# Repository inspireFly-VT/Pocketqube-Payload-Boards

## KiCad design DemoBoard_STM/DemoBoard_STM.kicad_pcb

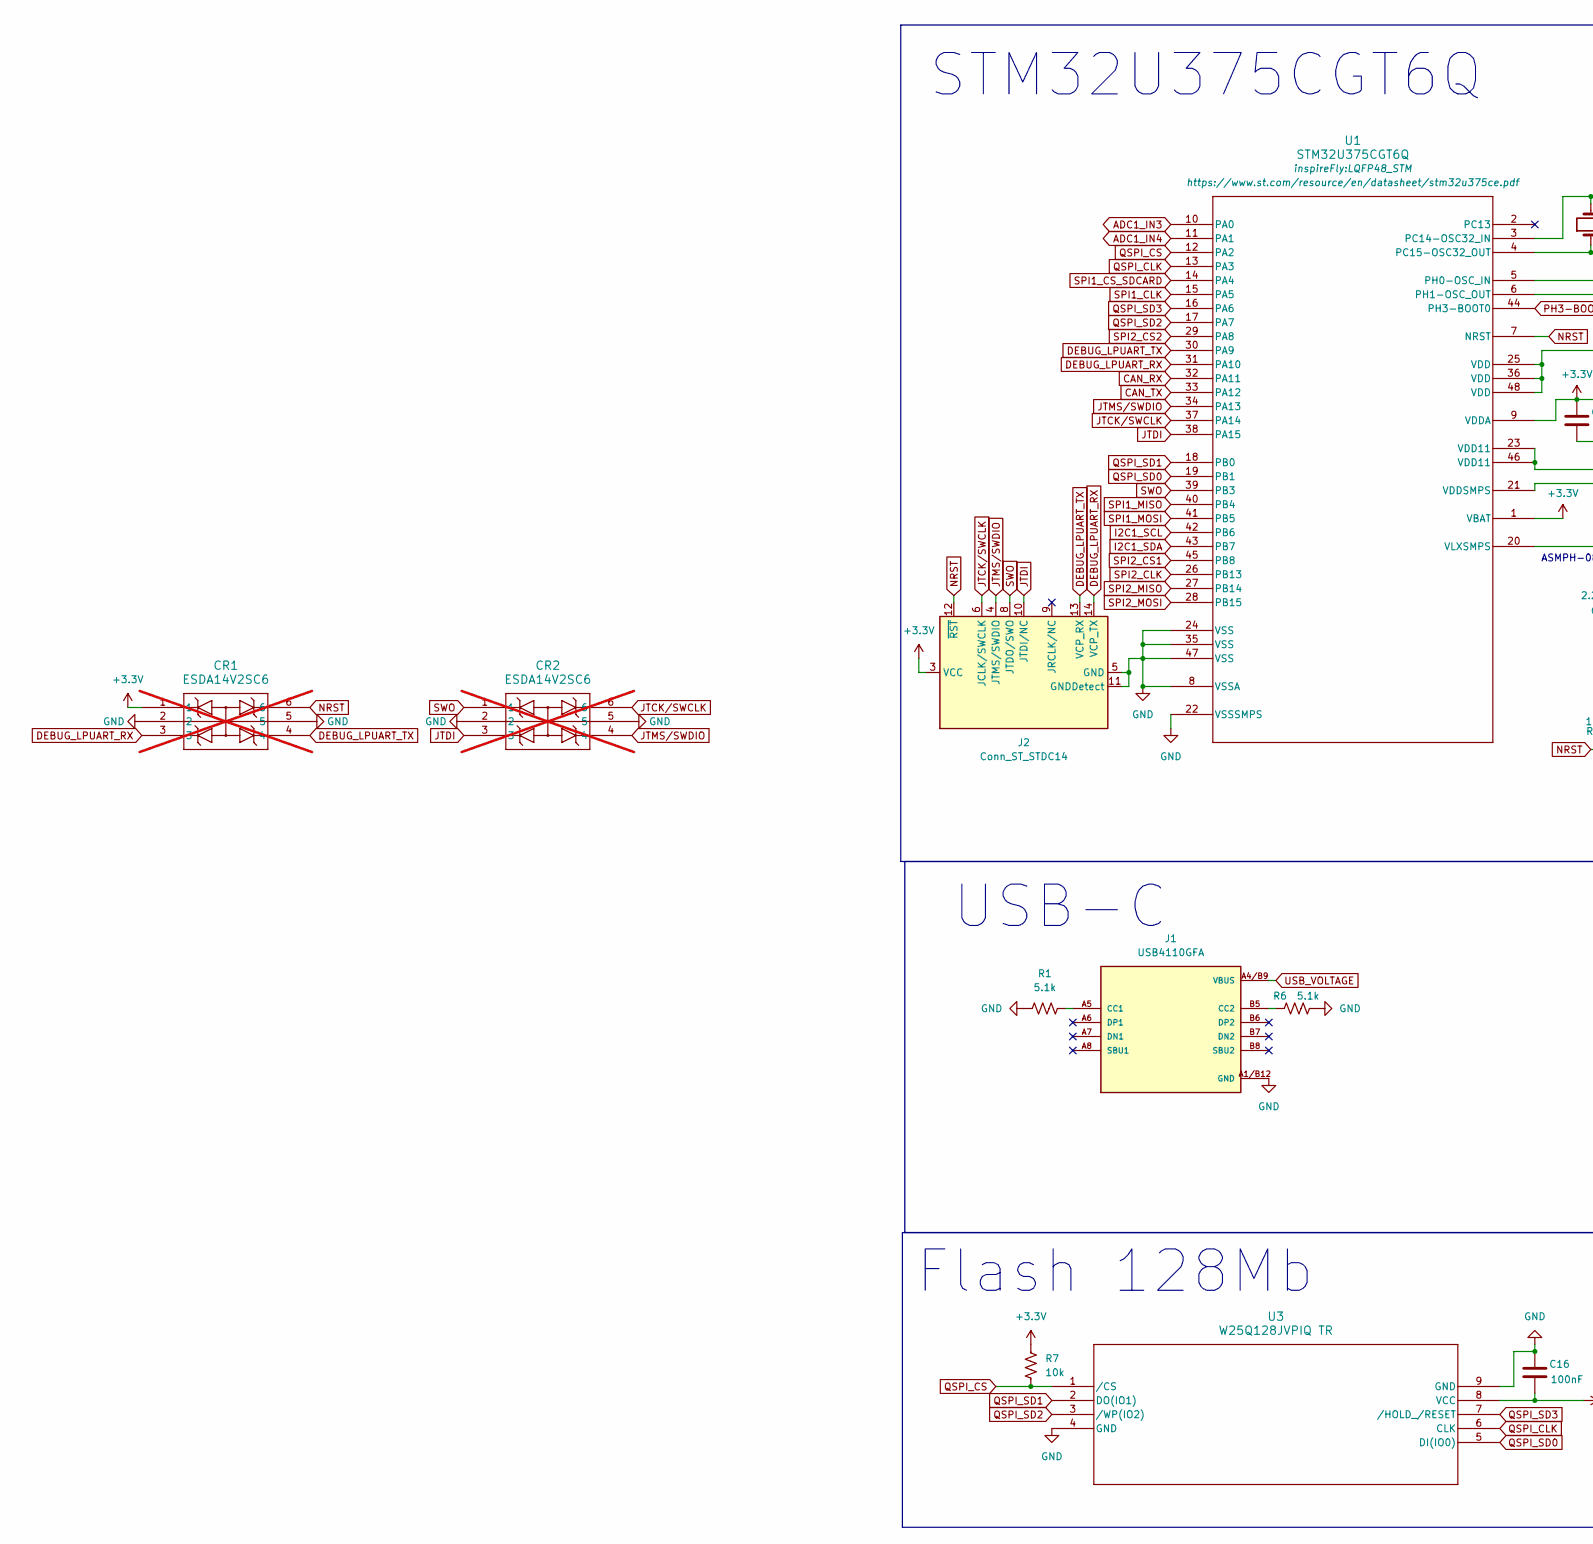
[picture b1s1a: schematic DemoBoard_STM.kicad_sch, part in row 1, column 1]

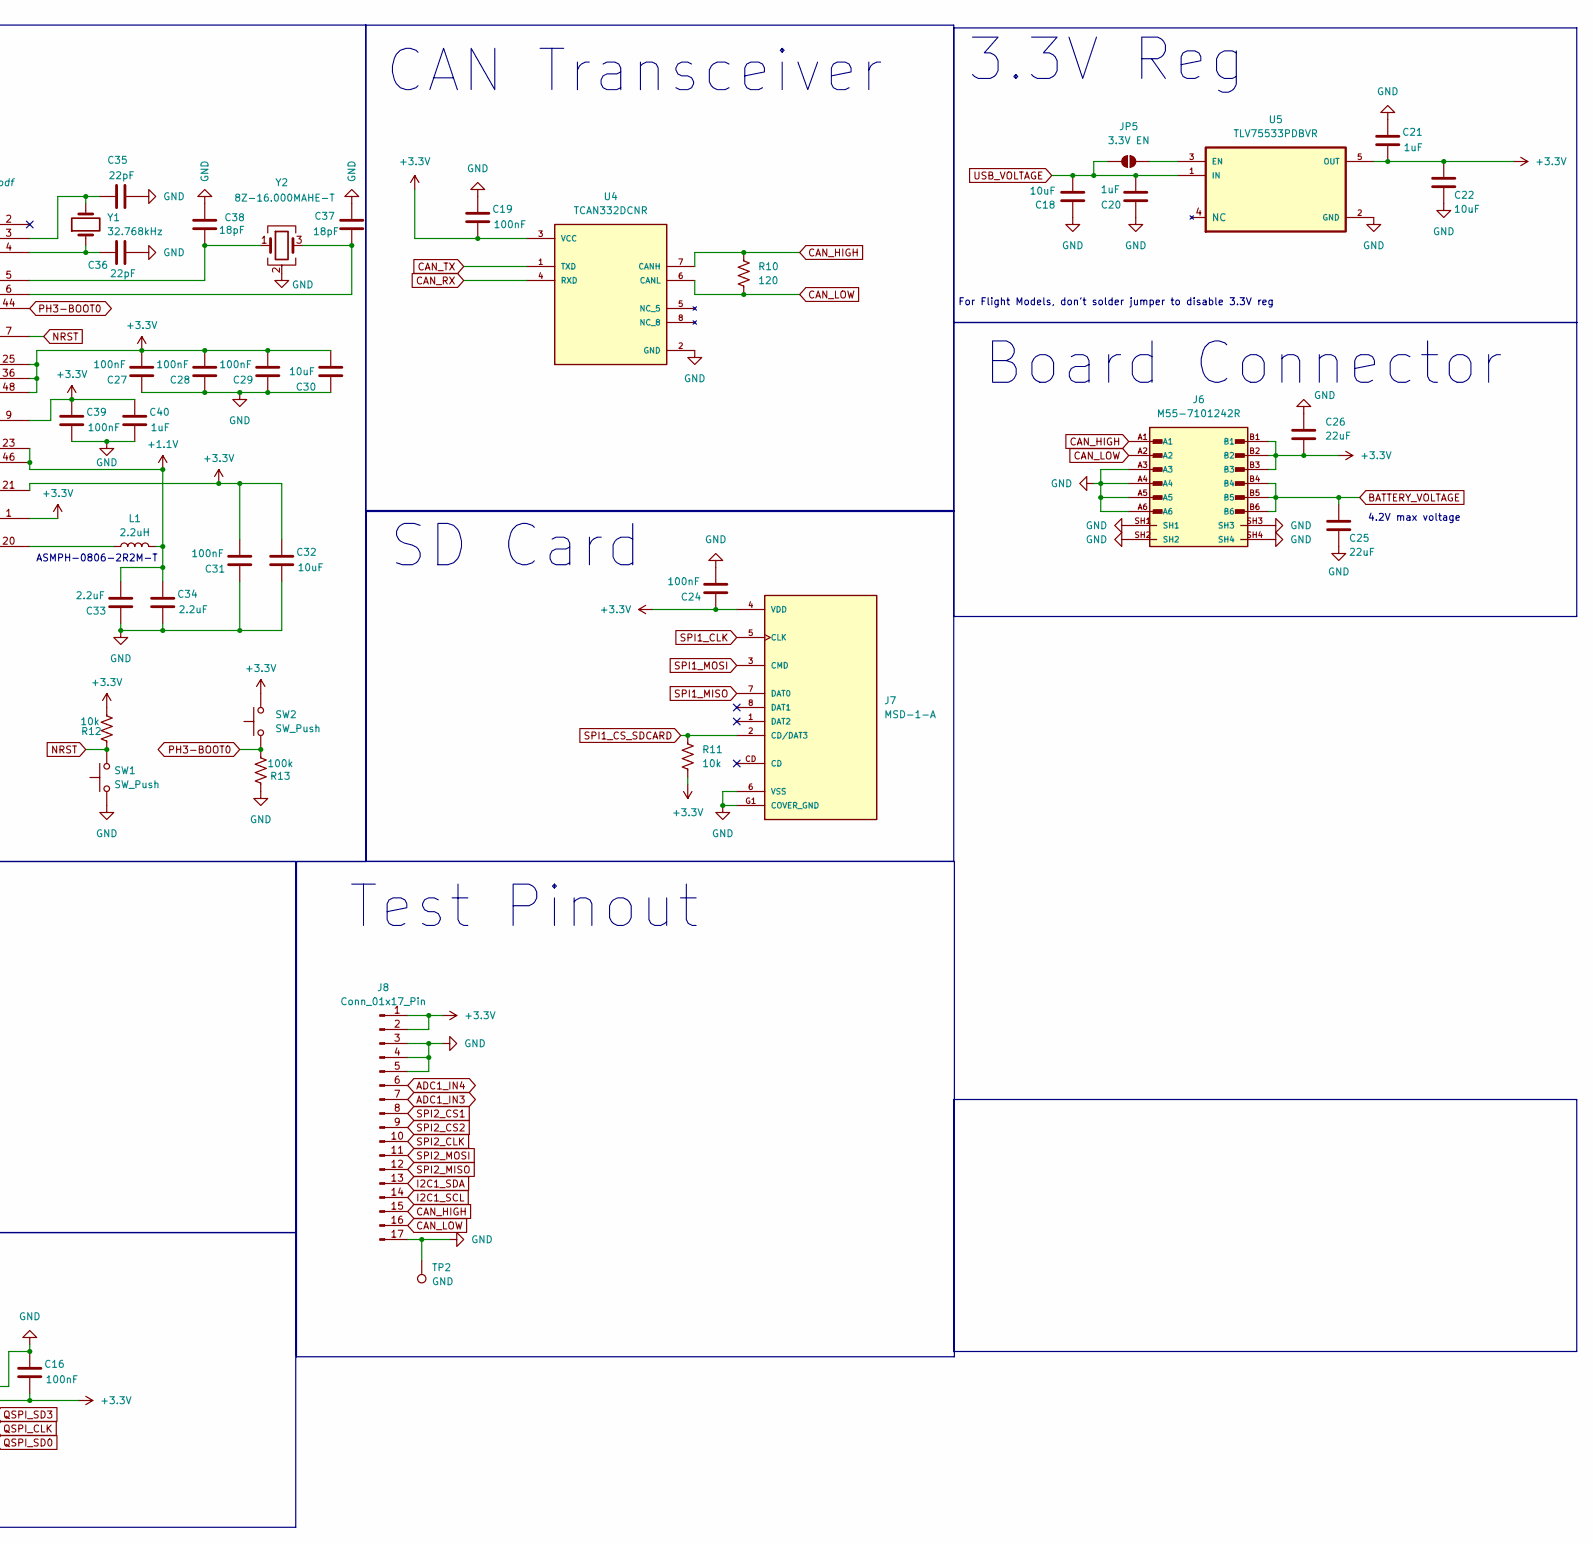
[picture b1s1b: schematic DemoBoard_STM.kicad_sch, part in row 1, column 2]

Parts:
C16, C19, C24, C27, C28, C29, C31, C39: 100nF; C_0402_1005Metric_Pad0.74x0.62mm_HandSolder
C18, C22, C30, C32: 10uF; C_0603_1608Metric
C20, C21, C40: 1uF; C_0402_1005Metric_Pad0.74x0.62mm_HandSolder
C25, C26: 22uF; C_1210_3225Metric
C33, C34: 2.2uF; C_0402_1005Metric_Pad0.74x0.62mm_HandSolder
C35, C36: 22pF; C_0402_1005Metric_Pad0.74x0.62mm_HandSolder
C37, C38: 18pF; C_0402_1005Metric_Pad0.74x0.62mm_HandSolder
CR1, CR2: ESDA14V2SC6; SOT23-6_1P75X3P05X0P95_STM; not fitted
J1: USB4110GFA; GCT_USB4110GFA; DigiKey_Part_Number 2073-USB4110-GF-A-1-ND
J2: Conn_ST_STDC14; SAMTEC_FTSH-107-01-L-DV-K-A
J6: M55-7101242R; HARWIN_M55-7101242R; PARTREV 7; DigiKey_Part_Number 952-3891-1-ND
J7: MSD-1-A; CUI_MSD-1-A; PARTREV 1.0; DigiKey_Part_Number 2223-MSD-1-ACT-ND
J8: Conn_01x17_Pin; PinSocket_1x17_P2.54mm_Vertical
JP5: 3.3V EN; SmallJumper
L1: 2.2uH; INDC1608X95N
R1, R6: 5.1k; R_0402_1005Metric_Pad0.72x0.64mm_HandSolder
R7, R11, R12: 10k; R_0402_1005Metric_Pad0.72x0.64mm_HandSolder
R10: 120; R_0402_1005Metric_Pad0.72x0.64mm_HandSolder
R13: 100k; R_0402_1005Metric_Pad0.72x0.64mm_HandSolder
SW1, SW2: SW_Push; SW_TL1015AF160QG
TP2: GND; TestPoint_Pad_D1.0mm
U1: STM32U375CGT6Q; LQFP48_STM
U3: W25Q128JVPIQ TR; WSON-8_6X5_WIN
U4: TCAN332DCNR; SOT65P280X145-8N; PARTREV E; DigiKey_Part_Number 296-47355-1-ND
U5: TLV75533PDBVR; SOT-23-5; DigiKey_Part_Number 296-50411-1-ND
Y1: 32.768kHz; XTAL_ABS07-32.768KHZ-T
Y2: 8Z-16.000MAHE-T; Crystal_SMD_2520-4Pin_2.5x2.0mm

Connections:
+1.1V: C33.2, C34.1, L1.2, U1.23 (VDD11), U1.46 (VDD11)
+3.3V: C16.2, C19.2, C21.2, C22.1, C24.1, C26.2, C27.2, C28.2, C29.2, C30.2, C31.2, C32.1, C39.1, C40.1, CR1.1, J2.3 (VCC), J6.B1, J6.B2, J6.B3, J7.4 (VDD), J8.1, J8.2, R7.2, R11.1, R12.1, SW2.2, U1.1 (VBAT), U1.9 (VDDA), U1.21 (VDDSMPS), U1.25 (VDD), U1.36 (VDD), U1.48 (VDD), U3.8 (VCC), U4.3 (VCC), U5.5 (OUT); also elsewhere on the board
ADC1_IN3: J8.7, U1.10 (PA0)
ADC1_IN4: J8.6, U1.11 (PA1)
BATTERY_VOLTAGE: C25.1, J6.B4, J6.B5, J6.B6
CAN_HIGH: J6.A1, J8.15, R10.1, U4.7 (CANH)
CAN_LOW: J6.A2, J8.16, R10.2, U4.6 (CANL)
CAN_RX: U1.32 (PA11), U4.4 (RXD)
CAN_TX: U1.33 (PA12), U4.1 (TXD)
DEBUG_LPUART_RX: CR1.3, J2.14 (VCP_TX), U1.31 (PA10)
DEBUG_LPUART_TX: CR1.4, J2.13 (VCP_RX), U1.30 (PA9)
GND: C16.1, C18.1, C19.1, C20.1, C21.1, C22.2, C24.2, C25.2, C26.1, C27.1, C28.1, C29.1, C30.1, C31.1, C32.2, C33.1, C34.2, C35.2, C36.1, C37.2, C38.1, C39.2, C40.2, CR1.2, CR1.5, CR2.2, CR2.5, J1.A1/B12 (GND), J1.B1/A12 (GND), J1.S1 (GND), J1.S2 (GND), J1.S3 (GND), J1.S4 (GND), J2.5 (GND), J2.7 (GND), J2.11 (GNDDetect), J6.A3, J6.A4, J6.A5, J6.A6, J6.SH1, J6.SH2, J6.SH3, J6.SH4, J7.6 (VSS), J7.G1 (COVER_GND), J7.G2 (COVER_GND), J7.G3 (COVER_GND), J7.G4 (COVER_GND), J8.3, J8.4, J8.5, J8.17, R1.2, R6.2, R13.2, SW1.1, TP2.1 (1_1), U1.8 (VSSA), U1.22 (VSSSMPS), U1.24 (VSS), U1.35 (VSS), U1.47 (VSS), U3.4 (GND), U3.9 (GND), U4.2 (GND), U5.2 (GND), Y2.2 (G), Y2.4 (G)
I2C1_SCL: J8.14, U1.42 (PB6)
I2C1_SDA: J8.13, U1.43 (PB7)
JTCK/SWCLK: CR2.6, J2.6 (JCLK/SWCLK), U1.37 (PA14)
JTDI: CR2.3, J2.10 (JTDI/NC), U1.38 (PA15)
JTMS/SWDIO: CR2.4, J2.4 (JTMS/SWDIO), U1.34 (PA13)
NRST: CR1.6, J2.12 (~RST), R12.2, SW1.2, U1.7 (NRST)
unnamed: J1.A5 (CC1), R1.1
unnamed: J1.B5 (CC2), R6.1
unnamed: JP5.2 (B), U5.3 (EN)
unnamed: C35.1, U1.3 (PC14-OSC32_IN), Y1.2
unnamed: C36.2, U1.4 (PC15-OSC32_OUT), Y1.1
unnamed: C38.2, U1.5 (PH0-OSC_IN), Y2.1
unnamed: C37.1, U1.6 (PH1-OSC_OUT), Y2.3
unnamed: L1.1, U1.20 (VLXSMPS)
PH3-BOOT0: R13.1, SW2.1, U1.44 (PH3-BOOT0)
QSPI_CLK: U1.13 (PA3), U3.6 (CLK)
QSPI_CS: R7.1, U1.12 (PA2), U3.1 (/CS)
QSPI_SD0: U1.19 (PB1), U3.5 (DI(IO0))
QSPI_SD1: U1.18 (PB0), U3.2 (DO(IO1))
QSPI_SD2: U1.17 (PA7), U3.3 (/WP(IO2))
QSPI_SD3: U1.16 (PA6), U3.7 (/HOLD_/RESET)
SPI1_CLK: J7.5 (CLK), U1.15 (PA5)
SPI1_CS_SDCARD: J7.2 (CD/DAT3), R11.2, U1.14 (PA4)
SPI1_MISO: J7.7 (DAT0), U1.40 (PB4)
SPI1_MOSI: J7.3 (CMD), U1.41 (PB5)
SPI2_CLK: J8.10, U1.26 (PB13)
SPI2_CS1: J8.8, U1.45 (PB8)
SPI2_CS2: J8.9, U1.29 (PA8)
SPI2_MISO: J8.12, U1.27 (PB14)
SPI2_MOSI: J8.11, U1.28 (PB15)
SWO: CR2.1, J2.8 (JTDO/SWO), U1.39 (PB3)
USB_VOLTAGE: C18.2, C20.2, J1.A4/B9 (VBUS), J1.B4/A9 (VBUS), JP5.1 (A), U5.1 (IN)

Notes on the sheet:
ASMPH-0806-2R2M-T
CAN Transceiver
USB-C
4.2V max voltage
SD Card
Board Connector
STM32U375CGT6Q
Test Pinout
For Flight Models, don't solder jumper to disable 3.3V reg
3.3V Reg
Flash 128Mb

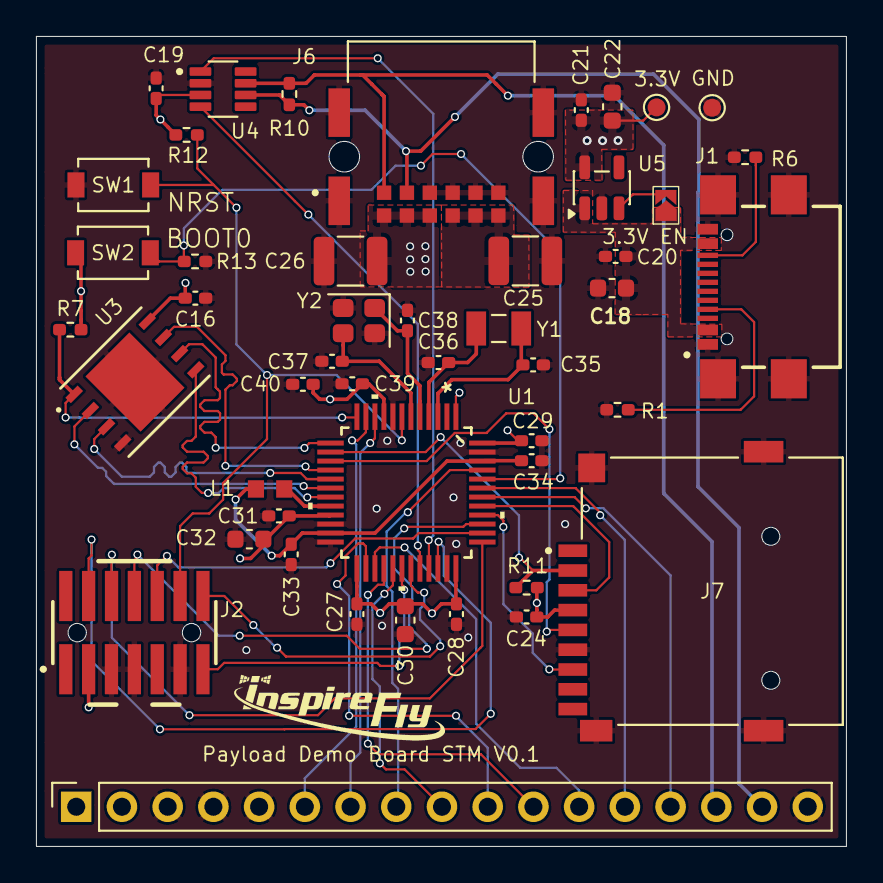
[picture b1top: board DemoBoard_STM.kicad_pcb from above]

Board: 4 copper layers, 45.0 x 45.0 mm, 47 parts (0 on the bottom side), 44 nets.

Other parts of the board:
TP3: 3.3V; TestPoint_Pad_D1.0mm

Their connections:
+3.3V: TP3.1; also elsewhere on the board

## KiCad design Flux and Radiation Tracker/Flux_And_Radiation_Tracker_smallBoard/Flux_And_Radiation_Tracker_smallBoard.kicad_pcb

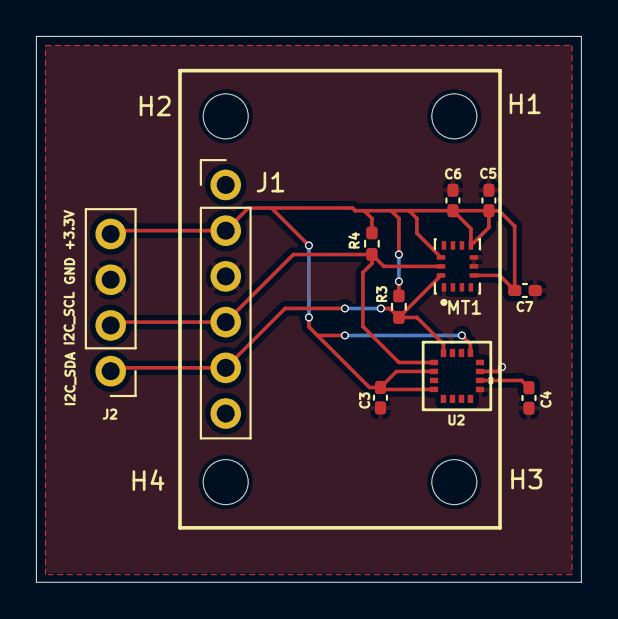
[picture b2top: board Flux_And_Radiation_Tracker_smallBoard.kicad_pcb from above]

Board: 2 copper layers, 30.3 x 30.3 mm, 15 parts (0 on the bottom side), 5 nets.

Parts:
C3: 1u; C_0402_1005Metric_Pad0.74x0.62mm_HandSolder
C4: 10u; C_0402_1005Metric_Pad0.74x0.62mm_HandSolder
C5: 0.1u; C_0402_1005Metric_Pad0.74x0.62mm_HandSolder
C6: 2.2u; C_0402_1005Metric_Pad0.74x0.62mm_HandSolder
C7: 10n; C_0402_1005Metric_Pad0.74x0.62mm_HandSolder
H1, H2, H3, H4: MountingHole; MountingHole_2.5mm
J1: Conn_01x06_Pin; PinHeader_1x06_P2.54mm_Vertical
J2: Conn_01x04_Pin; PinHeader_1x04_P2.54mm_Vertical
MT1: ICM-42670-P; XDCR_ICM-42670-P
R3, R4: 10k; R_0402_1005Metric_Pad0.72x0.64mm_HandSolder
U2: MMC5983MA; MMC5983MA_MEM

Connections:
+3.3V: C3.1, C5.1, C6.1, C7.1, J1.2, J2.4, MT1.5 (VDDIO), MT1.8 (VDD), MT1.12 (AP_CS), R3.1, R4.1, U2.2 (VDD), U2.4 (SPI_CS), U2.13 (VDDIO)
GND: C3.2, C4.2, C5.2, C6.2, C7.2, J1.3, J2.3, MT1.1 (AP_SDO/AP_AD0), MT1.6 (GND), MT1.7 (FSYNC), U2.9 (GND), U2.11 (GND)
I2C_SCL: J1.4, J2.2, MT1.13 (AP_SCL/AP_SCLK), R4.2, U2.1 (SCL/SPI_SCK)
I2C_SDA: J1.5, J2.1, MT1.14 (AP_SDA/AP_SDIO/AP_SDI), R3.2, U2.16 (SDA/SPI_SDI)
unnamed: C4.1, U2.10 (CAP)

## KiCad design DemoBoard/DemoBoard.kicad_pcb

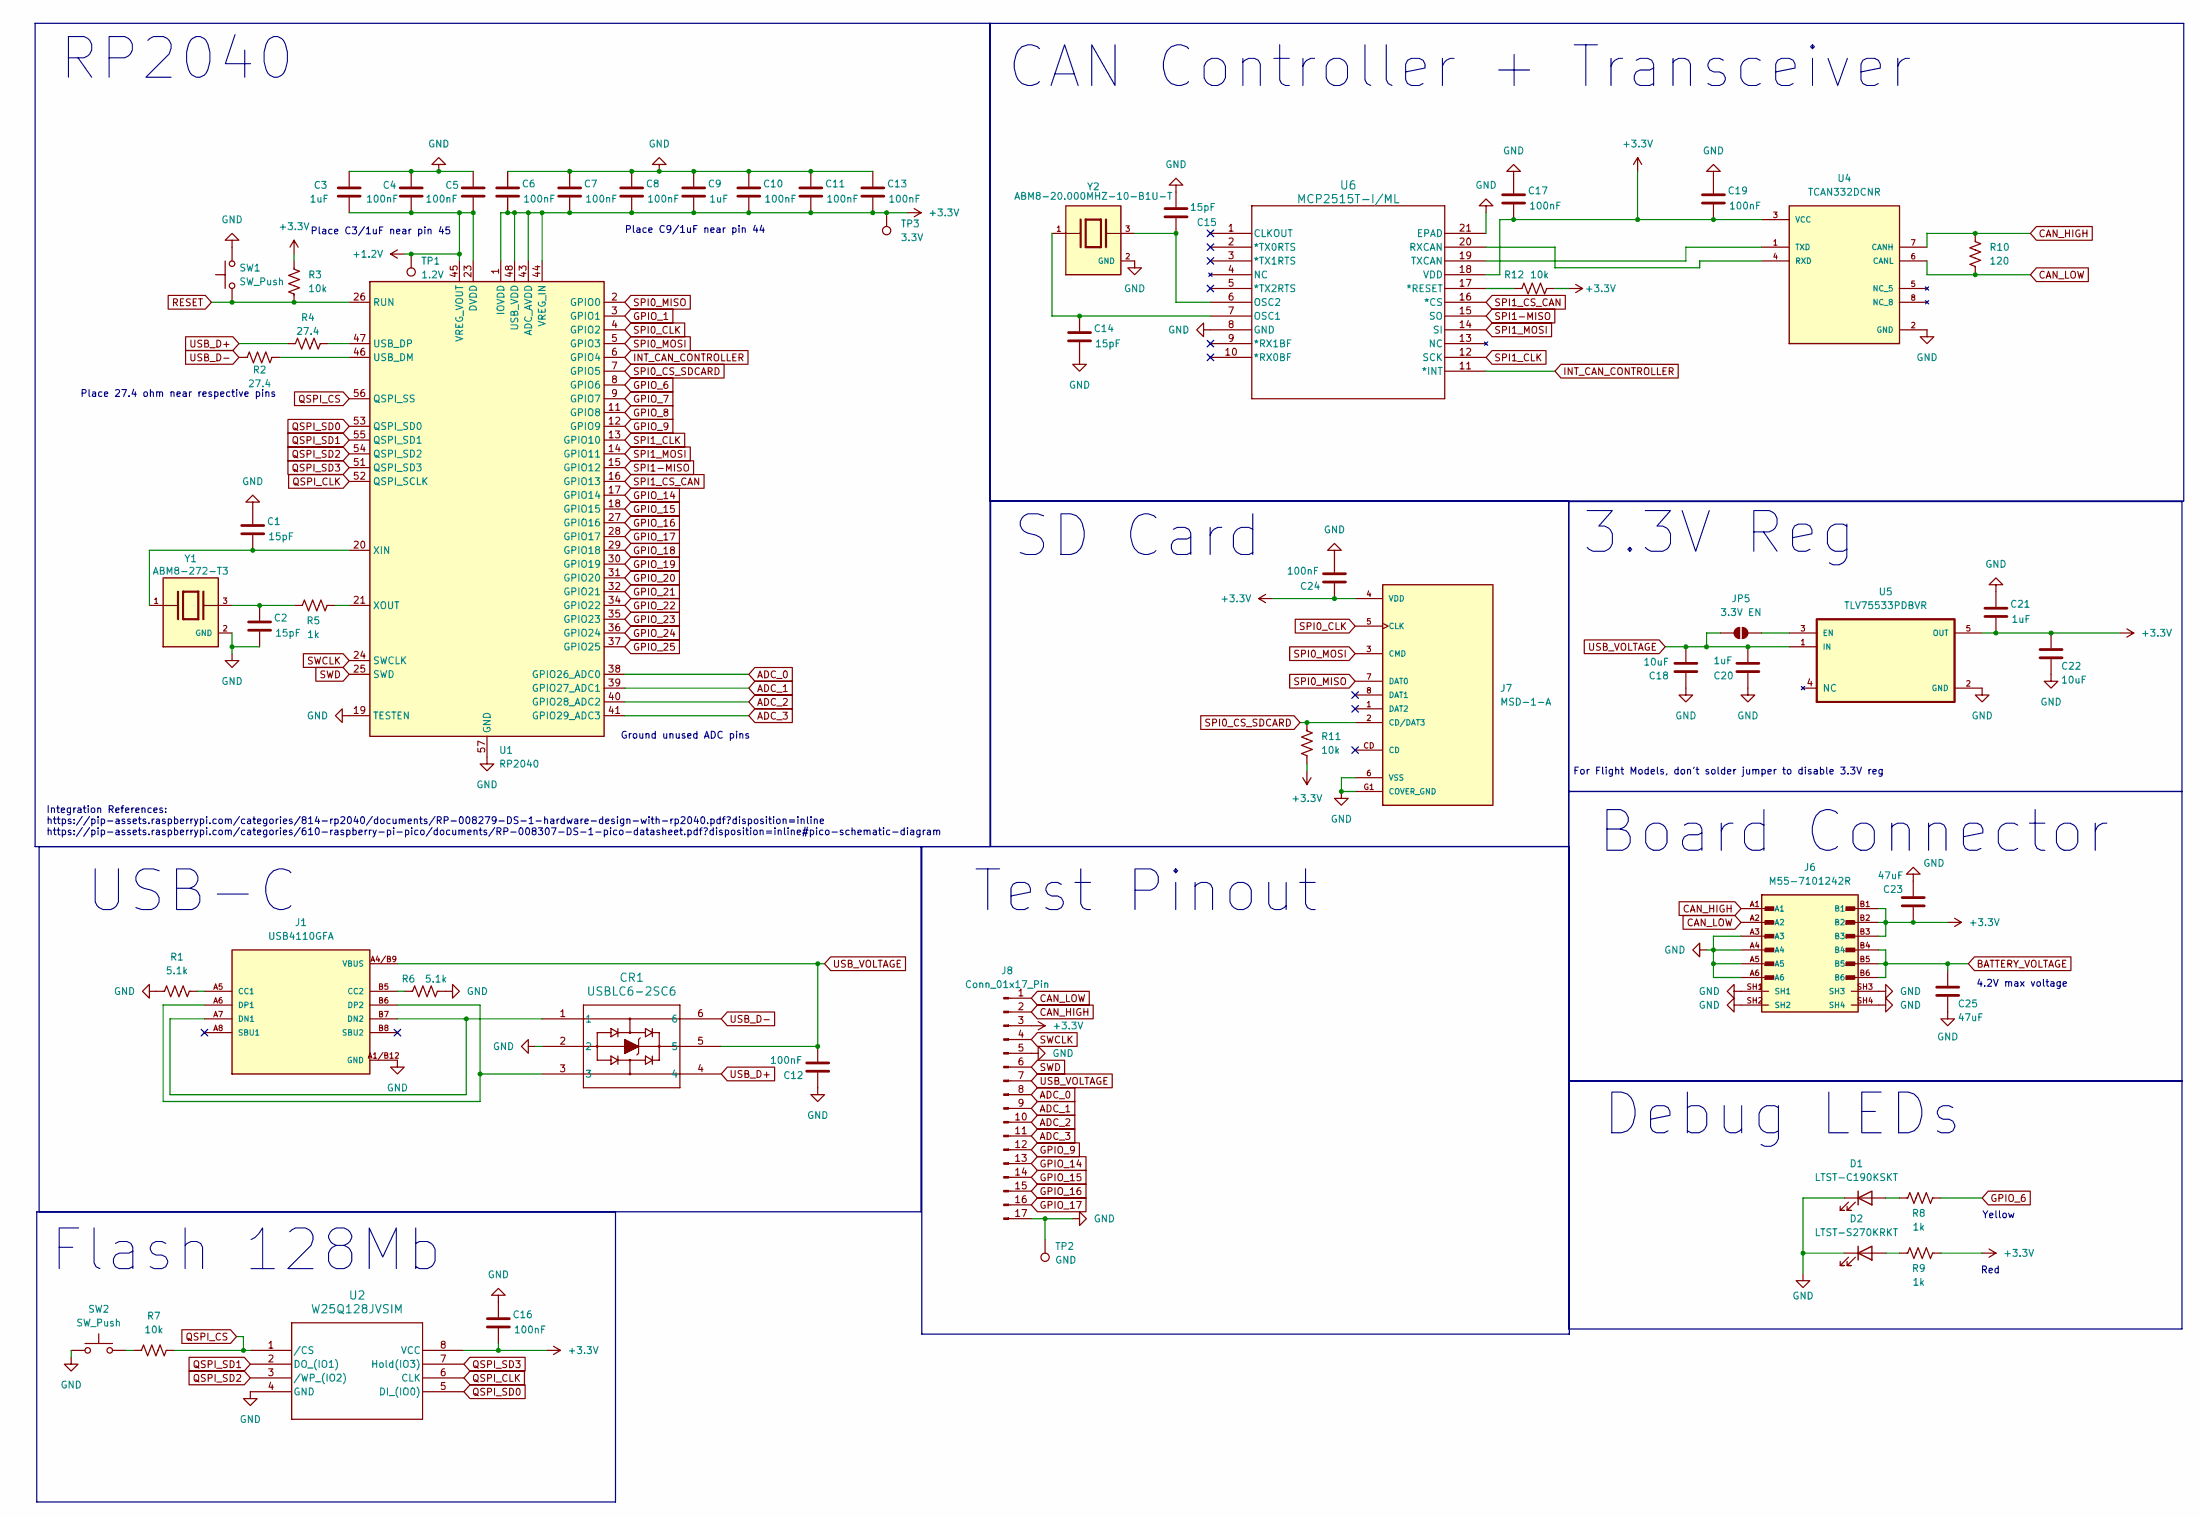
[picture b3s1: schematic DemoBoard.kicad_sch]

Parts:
C1, C2, C14, C15: 15pF; C_0402_1005Metric_Pad0.74x0.62mm_HandSolder
C3, C9, C20, C21: 1uF; C_0402_1005Metric_Pad0.74x0.62mm_HandSolder
C4, C5, C6, C7, C8, C10, C11, C12, C13, C16, C17, C19, C24: 100nF; C_0402_1005Metric_Pad0.74x0.62mm_HandSolder
C18, C22: 10uF; C_0402_1005Metric_Pad0.74x0.62mm_HandSolder
C23, C25: 47uF; C_1206_3216Metric_Pad1.33x1.80mm_HandSolder
CR1: USBLC6-2SC6; SOT-23-6
D1: LTST-C190KSKT; LED_0603_1608Metric_Pad1.05x0.95mm_HandSolder
D2: LTST-S270KRKT; LED_0603_1608Metric_Pad1.05x0.95mm_HandSolder
J1: USB4110GFA; GCT_USB4110GFA; DigiKey_Part_Number 2073-USB4110-GF-A-1-ND
J6: M55-7101242R; HARWIN_M55-7101242R; PARTREV 7; DigiKey_Part_Number 952-3891-1-ND
J7: MSD-1-A; CUI_MSD-1-A; PARTREV 1.0; DigiKey_Part_Number 2223-MSD-1-ACT-ND
J8: Conn_01x17_Pin; PinSocket_1x17_P2.54mm_Vertical
JP5: 3.3V EN; SmallJumper
R1, R6: 5.1k; R_0402_1005Metric_Pad0.72x0.64mm_HandSolder
R2, R4: 27.4; R_0402_1005Metric_Pad0.72x0.64mm_HandSolder
R3, R7, R11, R12: 10k; R_0402_1005Metric_Pad0.72x0.64mm_HandSolder
R5, R8, R9: 1k; R_0402_1005Metric_Pad0.72x0.64mm_HandSolder
R10: 120; R_0402_1005Metric_Pad0.72x0.64mm_HandSolder
SW1, SW2: SW_Push; SW_TL1015AF160QG
TP1: 1.2V; TestPoint_Pad_D1.0mm
TP2: GND; TestPoint_Pad_D1.0mm
TP3: 3.3V; TestPoint_Pad_D1.0mm
U1: RP2040; QFN-56-1EP_7x7mm_P0.4mm_EP3.2x3.2mm
U2: W25Q128JVSIM; SOIC_128JVSIM_WIN
U4: TCAN332DCNR; SOT65P280X145-8N; PARTREV E; DigiKey_Part_Number 296-47355-1-ND
U5: TLV75533PDBVR; SOT-23-5; DigiKey_Part_Number 296-50411-1-ND
U6: MCP2515T-I/ML; QFN20_4x4MC_MCH
Y1: ABM8-272-T3; XTAL_ABM8-272-T3; PARTREV 07-29-20; DigiKey_Part_Number 535-ABM8-272-T3CT-ND
Y2: ABM8-20.000MHZ-10-B1U-T; XTAL_ABM8-272-T3; PARTREV 07-29-20; DigiKey_Part_Number 535-ABM8-272-T3CT-ND

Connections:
+1.2V: C3.1, C4.1, C5.2, TP1.1 (1_1), U1.23 (DVDD), U1.45 (VREG_VOUT), U1.50 (DVDD)
+3.3V: C6.2, C7.2, C8.2, C9.2, C10.2, C11.2, C13.2, C16.2, C17.2, C19.2, C21.2, C22.1, C23.1, C24.1, J6.B1, J6.B2, J6.B3, J7.4 (VDD), J8.3, R3.2, R9.1, R11.1, R12.1, TP3.1 (1_1), U1.1 (IOVDD), U1.10 (IOVDD), U1.22 (IOVDD), U1.33 (IOVDD), U1.42 (IOVDD), U1.43 (ADC_AVDD), U1.44 (VREG_IN), U1.48 (USB_VDD), U1.49 (IOVDD), U2.8 (VCC), U4.3 (VCC), U5.5 (OUT), U6.18 (VDD)
ADC_0: J8.8, U1.38 (GPIO26_ADC0)
ADC_1: J8.9, U1.39 (GPIO27_ADC1)
ADC_2: J8.10, U1.40 (GPIO28_ADC2)
ADC_3: J8.11, U1.41 (GPIO29_ADC3)
BATTERY_VOLTAGE: C25.1, J6.B4, J6.B5, J6.B6
CAN_HIGH: J6.A1, J8.2, R10.1, U4.7 (CANH)
CAN_LOW: J6.A2, J8.1, R10.2, U4.6 (CANL)
GND: C1.1, C2.2, C3.2, C4.2, C5.1, C6.1, C7.1, C8.1, C9.1, C10.1, C11.1, C12.1, C13.1, C14.2, C15.2, C16.1, C17.1, C18.1, C19.1, C20.1, C21.1, C22.2, C23.2, C24.2, C25.2, CR1.2, D1.1 (K), D2.1 (K), J1.A1/B12 (GND), J1.B1/A12 (GND), J1.S1 (GND), J1.S2 (GND), J1.S3 (GND), J1.S4 (GND), J6.A3, J6.A4, J6.A5, J6.A6, J6.SH1, J6.SH2, J6.SH3, J6.SH4, J7.6 (VSS), J7.G1 (COVER_GND), J7.G2 (COVER_GND), J7.G3 (COVER_GND), J7.G4 (COVER_GND), J8.5, J8.17, R1.2, R6.2, SW1.2, SW2.1, TP2.1 (1_1), U1.19 (TESTEN), U1.57 (GND), U2.4 (GND), U4.2 (GND), U5.2 (GND), U6.8 (GND), U6.21 (EPAD), Y1.2 (GND), Y1.4 (GND), Y2.2 (GND), Y2.4 (GND)
GPIO_1: U1.3 (GPIO1)
GPIO_6: R8.1, U1.8 (GPIO6)
GPIO_7: U1.9 (GPIO7)
GPIO_8: U1.11 (GPIO8)
GPIO_9: J8.12, U1.12 (GPIO9)
GPIO_14: J8.13, U1.17 (GPIO14)
GPIO_15: J8.14, U1.18 (GPIO15)
GPIO_16: J8.15, U1.27 (GPIO16)
GPIO_17: J8.16, U1.28 (GPIO17)
GPIO_18: U1.29 (GPIO18)
GPIO_19: U1.30 (GPIO19)
GPIO_20: U1.31 (GPIO20)
GPIO_21: U1.32 (GPIO21)
GPIO_22: U1.34 (GPIO22)
GPIO_23: U1.35 (GPIO23)
GPIO_24: U1.36 (GPIO24)
GPIO_25: U1.37 (GPIO25)
INT_CAN_CONTROLLER: U1.6 (GPIO4), U6.11 (*INT)
unnamed: C2.1, R5.2, Y1.3
unnamed: D1.2 (A), R8.2
unnamed: D2.2 (A), R9.2
unnamed: J1.A5 (CC1), R1.1
unnamed: J1.B5 (CC2), R6.1
unnamed: CR1.1, J1.A7 (DN1), J1.B7 (DN2)
unnamed: CR1.3, J1.A6 (DP1), J1.B6 (DP2)
unnamed: JP5.2 (B), U5.3 (EN)
unnamed: R7.2, SW2.2
unnamed: R2.2, U1.46 (USB_DM)
unnamed: R4.2, U1.47 (USB_DP)
unnamed: C1.2, U1.20 (XIN), Y1.1
unnamed: R5.1, U1.21 (XOUT)
unnamed: U4.4 (RXD), U6.20 (RXCAN)
unnamed: U4.1 (TXD), U6.19 (TXCAN)
unnamed: R12.2, U6.17 (*RESET)
unnamed: C14.1, U6.7 (OSC1), Y2.1
unnamed: C15.1, U6.6 (OSC2), Y2.3
QSPI_CLK: U1.52 (QSPI_SCLK), U2.6 (CLK)
QSPI_CS: R7.1, U1.56 (QSPI_SS), U2.1 (/CS)
QSPI_SD0: U1.53 (QSPI_SD0), U2.5 (DI_(IO0))
QSPI_SD1: U1.55 (QSPI_SD1), U2.2 (DO_(IO1))
QSPI_SD2: U1.54 (QSPI_SD2), U2.3 (/WP_(IO2))
QSPI_SD3: U1.51 (QSPI_SD3), U2.7 (Hold(IO3))
RESET: R3.1, SW1.1, U1.26 (RUN)
SPI0_CLK: J7.5 (CLK), U1.4 (GPIO2)
SPI0_CS_SDCARD: J7.2 (CD/DAT3), R11.2, U1.7 (GPIO5)
SPI0_MISO: J7.7 (DAT0), U1.2 (GPIO0)
SPI0_MOSI: J7.3 (CMD), U1.5 (GPIO3)
SPI1-MISO: U1.15 (GPIO12), U6.15 (SO)
SPI1_CLK: U1.13 (GPIO10), U6.12 (SCK)
SPI1_CS_CAN: U1.16 (GPIO13), U6.16 (*CS)
SPI1_MOSI: U1.14 (GPIO11), U6.14 (SI)
SWCLK: J8.4, U1.24 (SWCLK)
SWD: J8.6, U1.25 (SWD)
USB_D+: CR1.4, R4.1
USB_D-: CR1.6, R2.1
USB_VOLTAGE: C12.2, C18.2, C20.2, CR1.5, J1.A4/B9 (VBUS), J1.B4/A9 (VBUS), J8.7, JP5.1 (A), U5.1 (IN)

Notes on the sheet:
Integration References: https://pip-assets.raspberrypi.com/categories/814-rp2040/documents/RP-008279-DS-1-hardware-design-with-rp2040.pdf?disposition=inline https://pip-assets.raspberrypi.com/categories/610-raspberry-pi-pico/documents/RP-008307-DS-1-pico-datasheet.pdf?disposition=inline#pico-schema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
CAN Controller + Transceiver
USB-C
Ground unused ADC pins
4.2V max voltage
Debug LEDs
SD Card
Place C3/1uF near pin 45
Board Connector
RP2040
Test Pinout
Place C9/1uF near pin 44
For Flight Models, don't solder jumper to disable 3.3V reg
Place 27.4 ohm near respective pins
3.3V Reg
Flash 128Mb
Red
Yellow

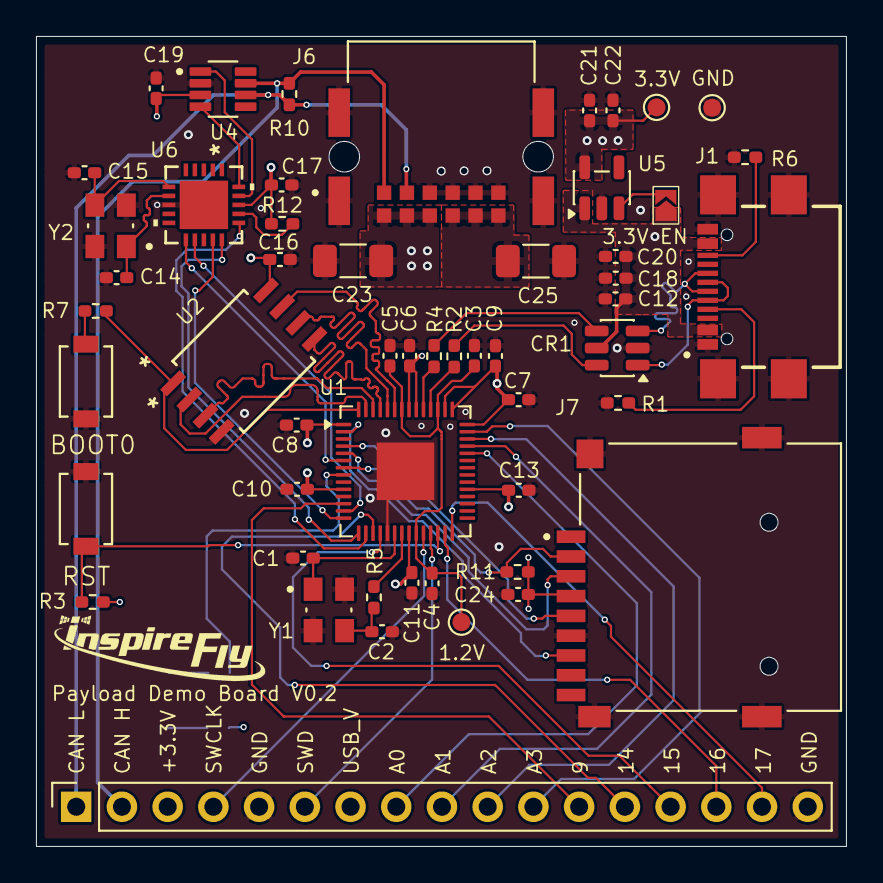
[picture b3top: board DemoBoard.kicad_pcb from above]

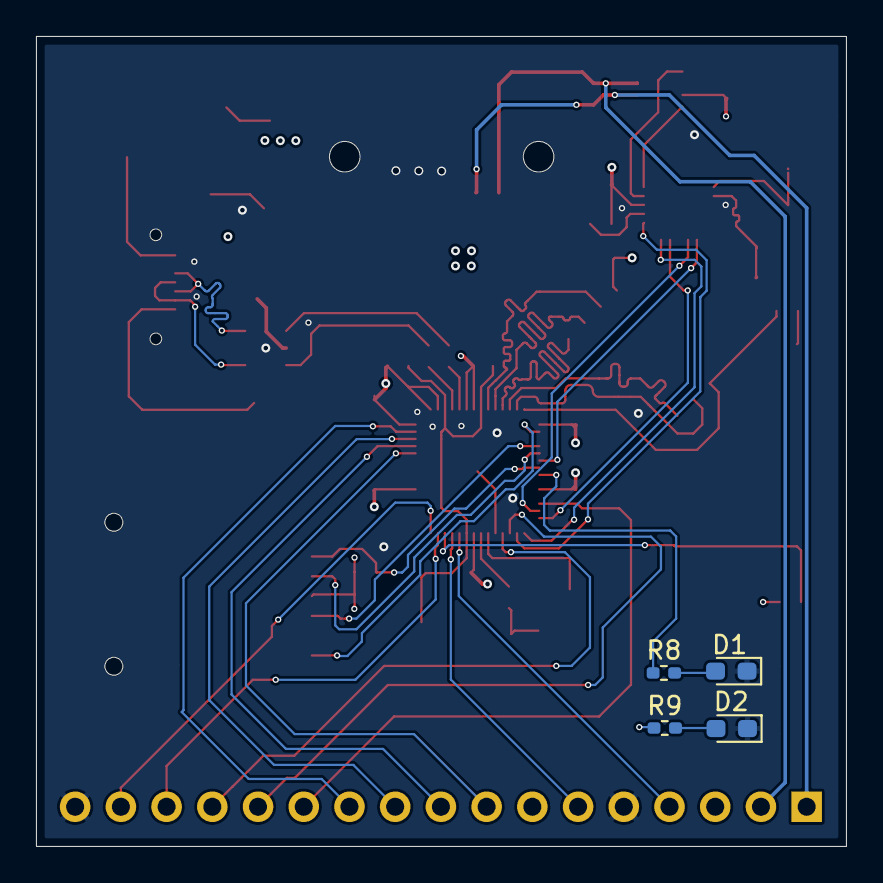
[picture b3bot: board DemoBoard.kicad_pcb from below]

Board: 4 copper layers, 45.0 x 45.0 mm, 57 parts (4 on the bottom side), 55 nets.

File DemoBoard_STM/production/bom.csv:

Designator,Footprint,Quantity,Value,LCSC Part #
"C1, C2",0402,2,15pF,
"C10, C11, C12, C13, C16, C17, C19, C24, C4, C5, C6, C7, C8",0402,13,100nF,
"C14, C15",0402,2,18pF,
"C18, C22",0402,2,10uF,
"C20, C21, C3, C9",0402,4,1uF,
"C23, C25",1206,2,47uF,
CR1,SOT-23-6,1,USBLC6-2SC6,
D1,0603,1,LTST-C190KSKT,
D2,0603,1,LTST-S270KRKT,
J1,GCT_USB4110GFA,1,USB4110GFA,
J6,HARWIN_M55-7101242R,1,M55-7101242R,
J7,CUI_MSD-1-A,1,MSD-1-A,
J8,PinSocket_1x17_P2.54mm_Vertical,1,Conn_01x17_Pin,
"R1, R6",0402,2,5.1k,
R10,0402,1,120,
"R11, R3, R7",0402,3,10k,
"R2, R4",0402,2,27.4,
"R5, R8, R9",0402,3,1k,
"SW1, SW2",SW_TL1015AF160QG,2,SW_Push,
TP1,TestPoint_Pad_D1.0mm,1,1.2V,
TP2,TestPoint_Pad_D1.0mm,1,GND,
TP3,TestPoint_Pad_D1.0mm,1,3.3V,
U1,QFN-56-1EP_7x7mm_P0.4mm_EP3.2x3.2mm,1,RP2040,
U2,SOIC_128JVSIM_WIN,1,W25Q128JVSIM,
U3,SON65P450X300X90-15N,1,MCP2518FDT-E_QBB,
U4,SOT65P280X145-8N,1,TCAN332DCNR,
U5,SOT-23-5,1,TLV75533PDBVR,
Y1,XTAL_ABM8-272-T3,1,ABM8-272-T3,
Y2,XTAL_ABM8-272-T3,1,ABM8-20.000MHZ-10-B1U-T,

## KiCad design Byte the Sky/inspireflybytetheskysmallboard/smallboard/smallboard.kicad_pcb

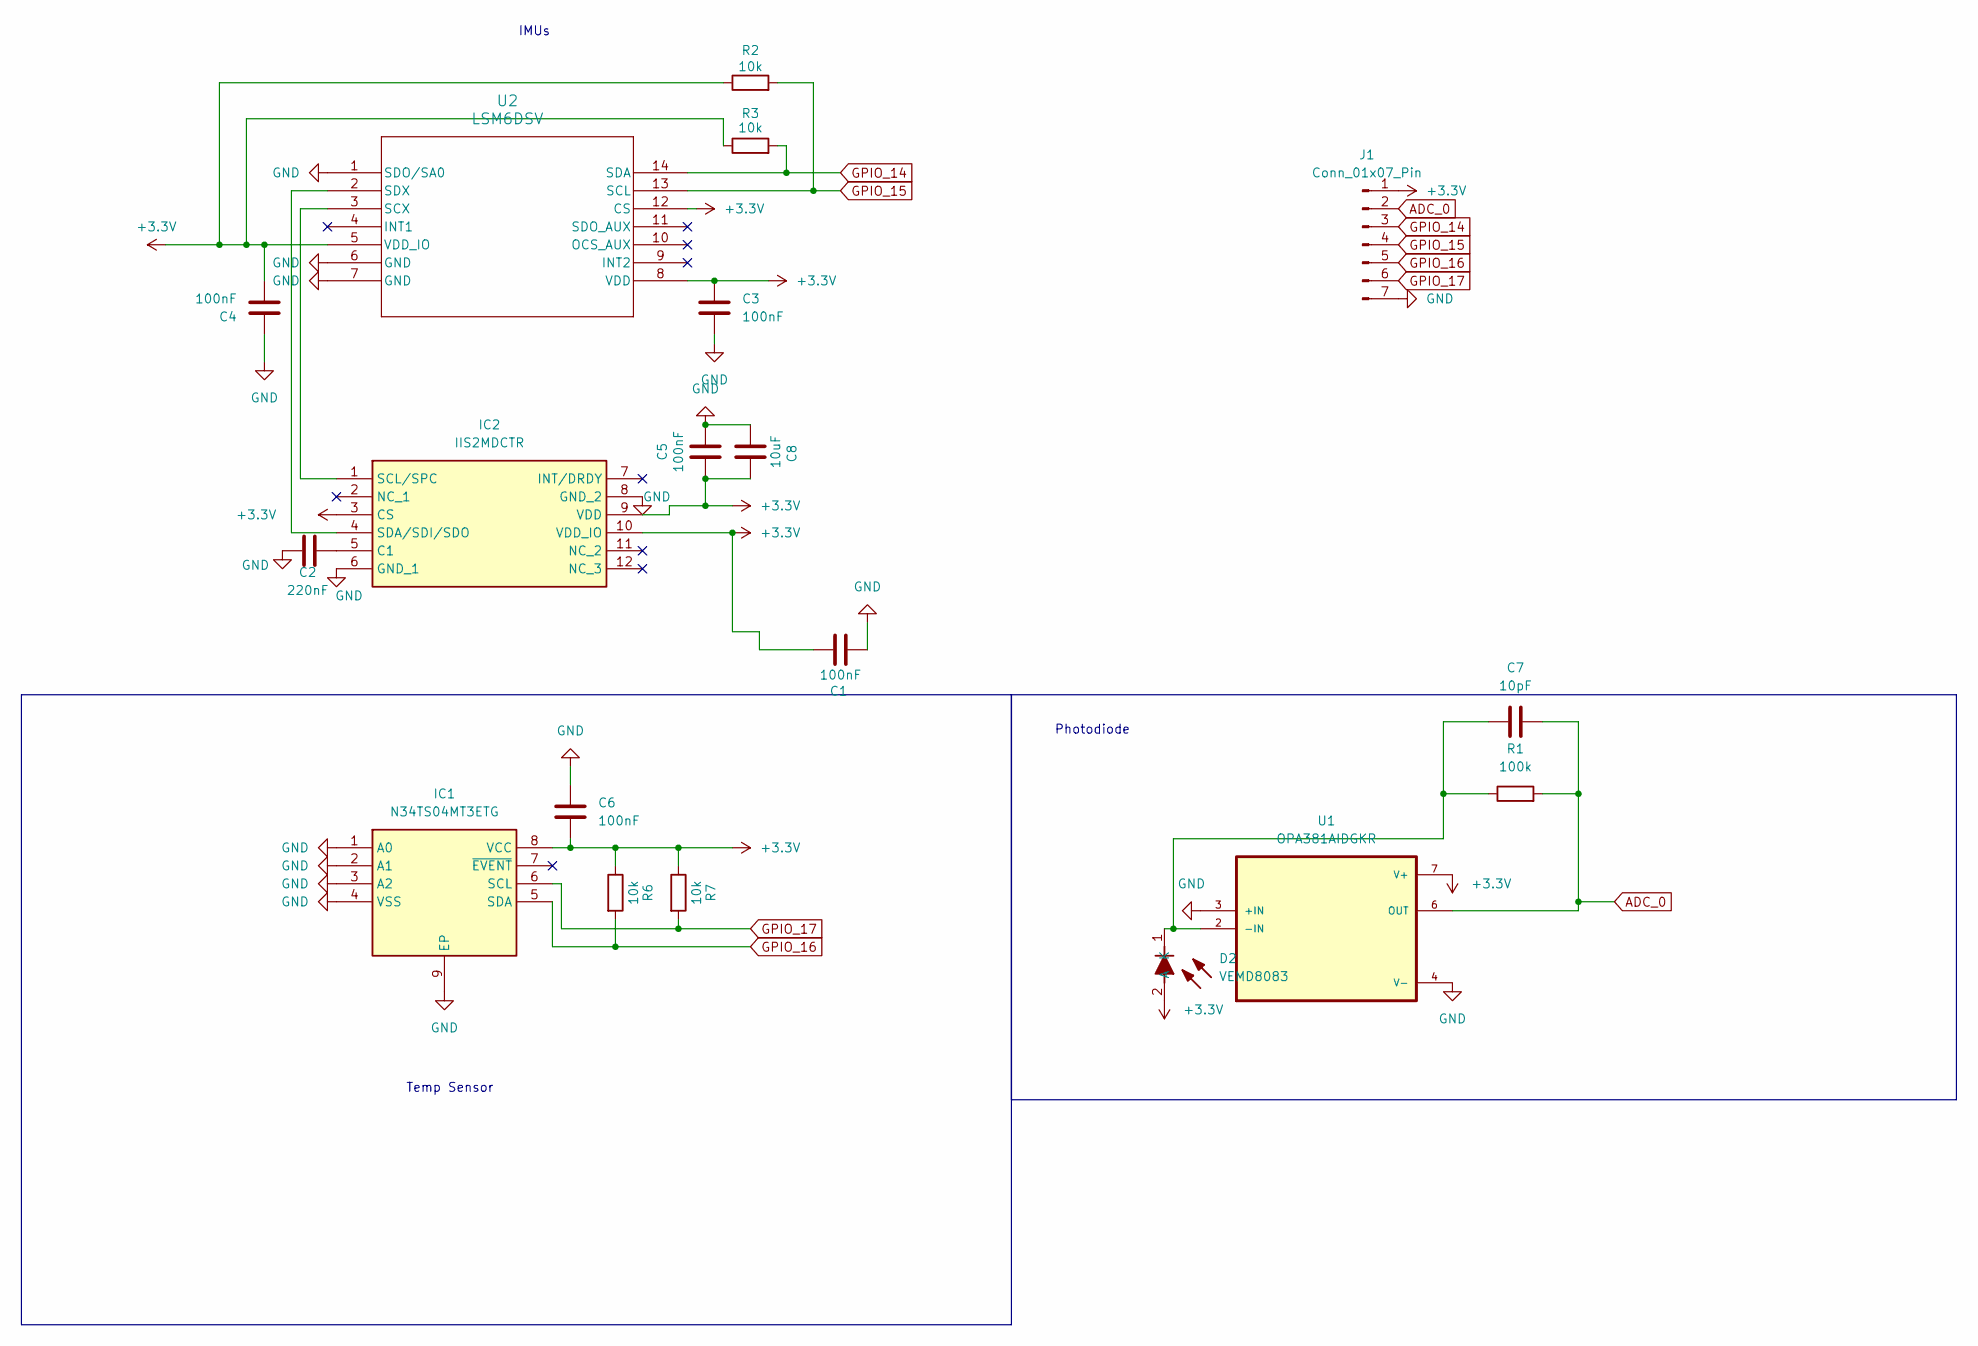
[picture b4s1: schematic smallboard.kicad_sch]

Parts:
C1, C3, C4, C5, C6: 100nF; C_0402_1005Metric_Pad0.74x0.62mm_HandSolder
C2: 220nF; C_0402_1005Metric_Pad0.74x0.62mm_HandSolder
C7: 10pF; C_0402_1005Metric_Pad0.74x0.62mm_HandSolder
C8: 10uF; C_0402_1005Metric_Pad0.74x0.62mm_HandSolder
D2: VEMD8083; Manufacturer_Part_Number VEMD8083
IC1: N34TS04MT3ETG; SON50P300X200X80-9N; Manufacturer_Part_Number N34TS04MT3ETG
IC2: IIS2MDCTR; Mouser Part Number 511-IIS2MDCTR
J1: Conn_01x07_Pin; PinHeader_1x07_P2.54mm_Vertical
R1: 100k; R_0402_1005Metric_Pad0.72x0.64mm_HandSolder
R2, R3, R6, R7: 10k; R_0402_1005Metric_Pad0.72x0.64mm_HandSolder
U1: OPA381AIDGKR; SOP65P490X110-8N; DigiKey_Part_Number 296-46163-1-ND
U2: LSM6DSV; LGA14-L_2P59X3P1X0P5_STM

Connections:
+3.3V: C1.1, C3.1, C4.2, C5.1, C6.2, C8.1, D2.2 (A), IC1.8 (VCC), IC2.3 (CS), IC2.9 (VDD), IC2.10 (VDD_IO), J1.1, R2.1, R3.1, R6.1, R7.1, U1.7 (V+), U2.5 (VDD_IO), U2.8 (VDD), U2.12 (CS)
ADC_0: C7.2, J1.2, R1.2, U1.6 (OUT)
GND: C1.2, C2.1, C3.2, C4.1, C5.2, C6.1, C8.2, IC1.1 (A0), IC1.2 (A1), IC1.3 (A2), IC1.4 (VSS), IC1.9 (EP), IC2.6 (GND_1), IC2.8 (GND_2), J1.7, U1.3 (+IN), U1.4 (V-), U2.1 (SDO/SA0), U2.6 (GND), U2.7 (GND)
GPIO_14: J1.3, R3.2, U2.14 (SDA)
GPIO_15: J1.4, R2.2, U2.13 (SCL)
GPIO_16: IC1.5 (SDA), J1.5, R6.2
GPIO_17: IC1.6 (SCL), J1.6, R7.2
unnamed: C7.1, D2.1 (K), R1.1, U1.2 (-IN)
unnamed: C2.2, IC2.5 (C1)
unnamed: IC2.1 (SCL/SPC), U2.3 (SCX)
unnamed: IC2.4 (SDA/SDI/SDO), U2.2 (SDX)

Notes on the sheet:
IMUs
Photodiode
Temp Sensor

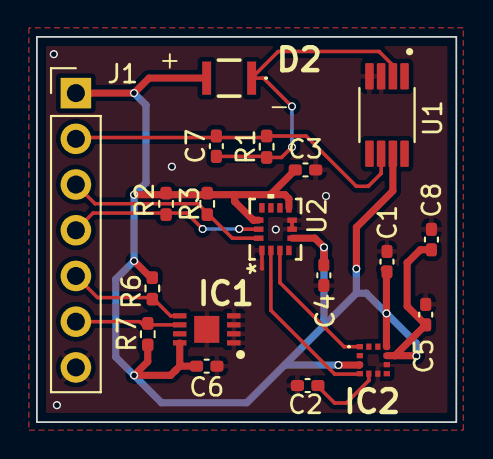
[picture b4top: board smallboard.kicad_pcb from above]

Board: 2 copper layers, 23.3 x 21.4 mm, 19 parts (0 on the bottom side), 11 nets.
